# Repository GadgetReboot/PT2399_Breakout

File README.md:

# PT2399_Breakout
PT2399 Echo IC Breakout Board 
<br><br><BR><BR>

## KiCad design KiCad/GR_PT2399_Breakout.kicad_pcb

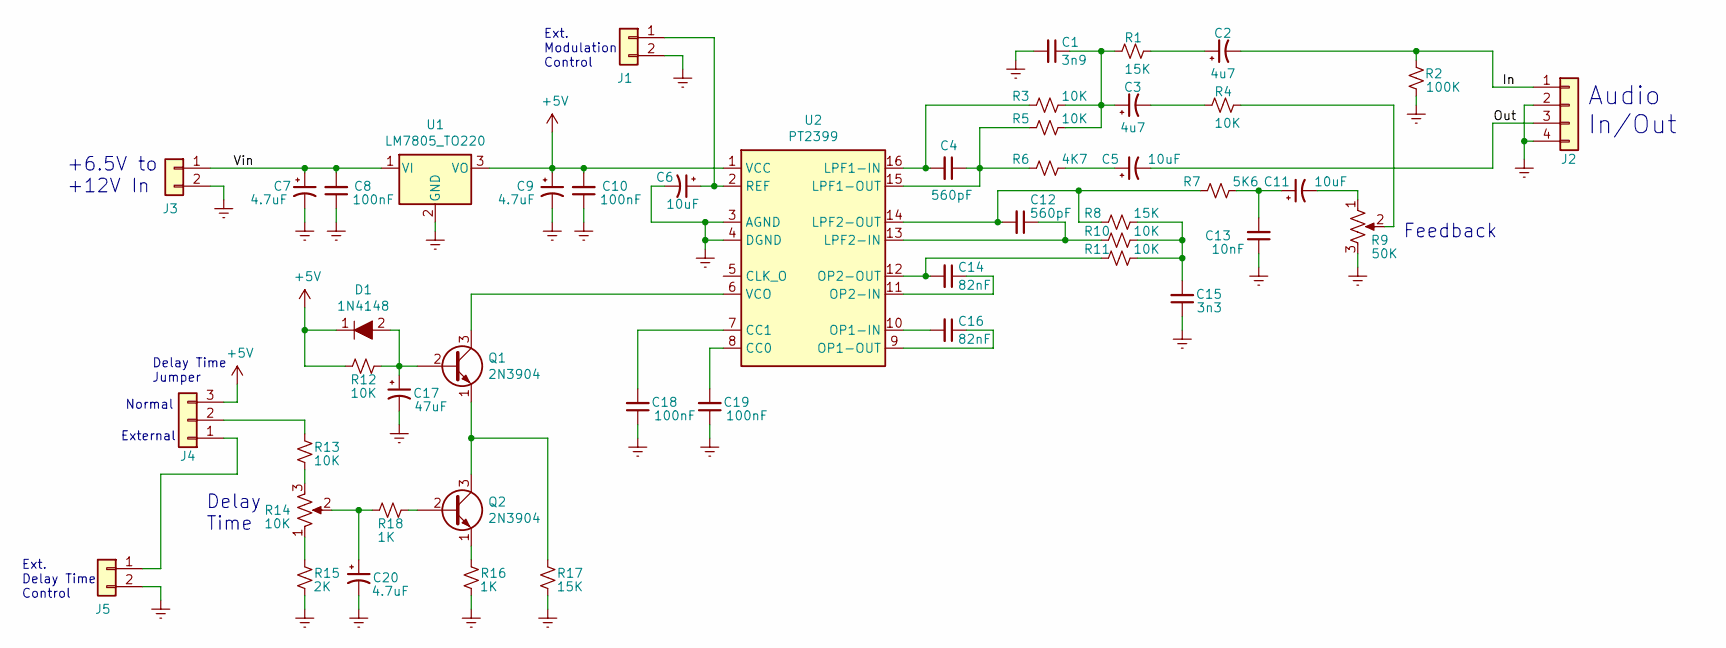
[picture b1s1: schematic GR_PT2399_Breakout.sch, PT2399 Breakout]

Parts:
C1: 3n9; C_Disc_D3.8mm_W2.6mm_P2.50mm
C2, C3: 4u7; CP_Radial_D5.0mm_P2.50mm
C4, C12: 560pF; C_Disc_D3.8mm_W2.6mm_P2.50mm
C5, C6, C11: 10uF; CP_Radial_D5.0mm_P2.50mm
C7, C9, C20: 4.7uF; CP_Radial_D5.0mm_P2.50mm
C8, C10, C18, C19: 100nF; C_Disc_D3.8mm_W2.6mm_P2.50mm
C13: 10nF; C_Disc_D3.8mm_W2.6mm_P2.50mm
C14, C16: 82nF; C_Disc_D3.8mm_W2.6mm_P2.50mm
C15: 3n3; C_Disc_D3.8mm_W2.6mm_P2.50mm
C17: 47uF; CP_Radial_D5.0mm_P2.50mm
D1: 1N4148; Diode_DO-35_P10mm; MPN 1N4148; Digi-Key_PN 1N4148FS-ND
J1, J3, J5: Conn_01x02; PinHeader_1x02_P2.54mm_Vertical
J2: Conn_01x04; PinHeader_1x04_P2.54mm_Vertical
J4: Conn_01x03; PinHeader_1x03_P2.54mm_Vertical
Q1, Q2: 2N3904; TO-92_Inline_Wide
R1, R8, R17: 15K; R_Axial_DIN0207_L6.3mm_D2.5mm_P10.16mm_Horizontal
R2: 100K; R_Axial_DIN0207_L6.3mm_D2.5mm_P10.16mm_Horizontal
R3, R4, R5, R10, R11, R12, R13: 10K; R_Axial_DIN0207_L6.3mm_D2.5mm_P10.16mm_Horizontal
R6: 4K7; R_Axial_DIN0207_L6.3mm_D2.5mm_P10.16mm_Horizontal
R7: 5K6; R_Axial_DIN0207_L6.3mm_D2.5mm_P10.16mm_Horizontal
R9: 50K; Potentiometer_Bourns_PTV09A-1
R14: 10K; Potentiometer_Bourns_PTV09A-1
R15: 2K; R_Axial_DIN0207_L6.3mm_D2.5mm_P10.16mm_Horizontal
R16, R18: 1K; R_Axial_DIN0207_L6.3mm_D2.5mm_P10.16mm_Horizontal
U1: LM7805_TO220; TO-220-3_Vertical
U2: PT2399; DIP-16_W7.62mm_Socket_LongPads

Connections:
+5V: C9.1, C10.2, D1.1, J4.3, R12.1, U1.3 (VO), U2.1 (VCC)
/In: C2.2, J2.1, R2.1
/Out: C5.2, J2.3
/Vin: C7.1, C8.2, J3.1, U1.1 (VI)
GNDREF: C1.2, C6.2, C7.2, C8.1, C9.2, C10.1, C13.1, C15.1, C17.2, C18.1, C19.1, C20.2, J1.2, J2.2, J2.4, J3.2, J5.2, R2.2, R9.3, R15.2, R16.2, R17.2, U1.2 (GND), U2.3 (AGND), U2.4 (DGND)
unnamed: C1.1, C3.1, R1.1, R3.2, R5.2
unnamed: C2.1, R1.2
unnamed: C3.2, R4.1
unnamed: C4.1, R5.1, R6.1, U2.15 (LPF1-OUT)
unnamed: C4.2, R3.1, U2.16 (LPF1-IN)
unnamed: C5.1, R6.2
unnamed: C6.1, J1.1, U2.2 (REF)
unnamed: C11.1, C13.2, R7.2
unnamed: C11.2, R9.1
unnamed: C12.1, R10.1, U2.13 (LPF2-IN)
unnamed: C12.2, R7.1, R8.1, U2.14 (LPF2-OUT)
unnamed: C14.1, U2.11 (OP2-IN)
unnamed: C14.2, R11.1, U2.12 (OP2-OUT)
unnamed: C15.2, R8.2, R10.2, R11.2
unnamed: C16.1, U2.9 (OP1-OUT)
unnamed: C16.2, U2.10 (OP1-IN)
unnamed: C17.1, D1.2, Q1.2 (B), R12.2
unnamed: C18.2, U2.7 (CC1)
unnamed: C19.2, U2.8 (CC0)
unnamed: C20.1, R14.2, R18.1
unnamed: J4.1, J5.1
unnamed: J4.2, R13.1
unnamed: Q1.1 (E), Q2.3 (C), R17.1
unnamed: Q1.3 (C), U2.6 (VCO)
unnamed: Q2.1 (E), R16.1
unnamed: Q2.2 (B), R18.2
unnamed: R4.2, R9.2
unnamed: R13.2, R14.3
unnamed: R14.1, R15.1

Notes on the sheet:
Audio In/Out
Delay Time Jumper
Delay Time
Normal
External
+6.5V to +12V In
Ext. Delay Time Control
Ext. Modulation Control
Feedback

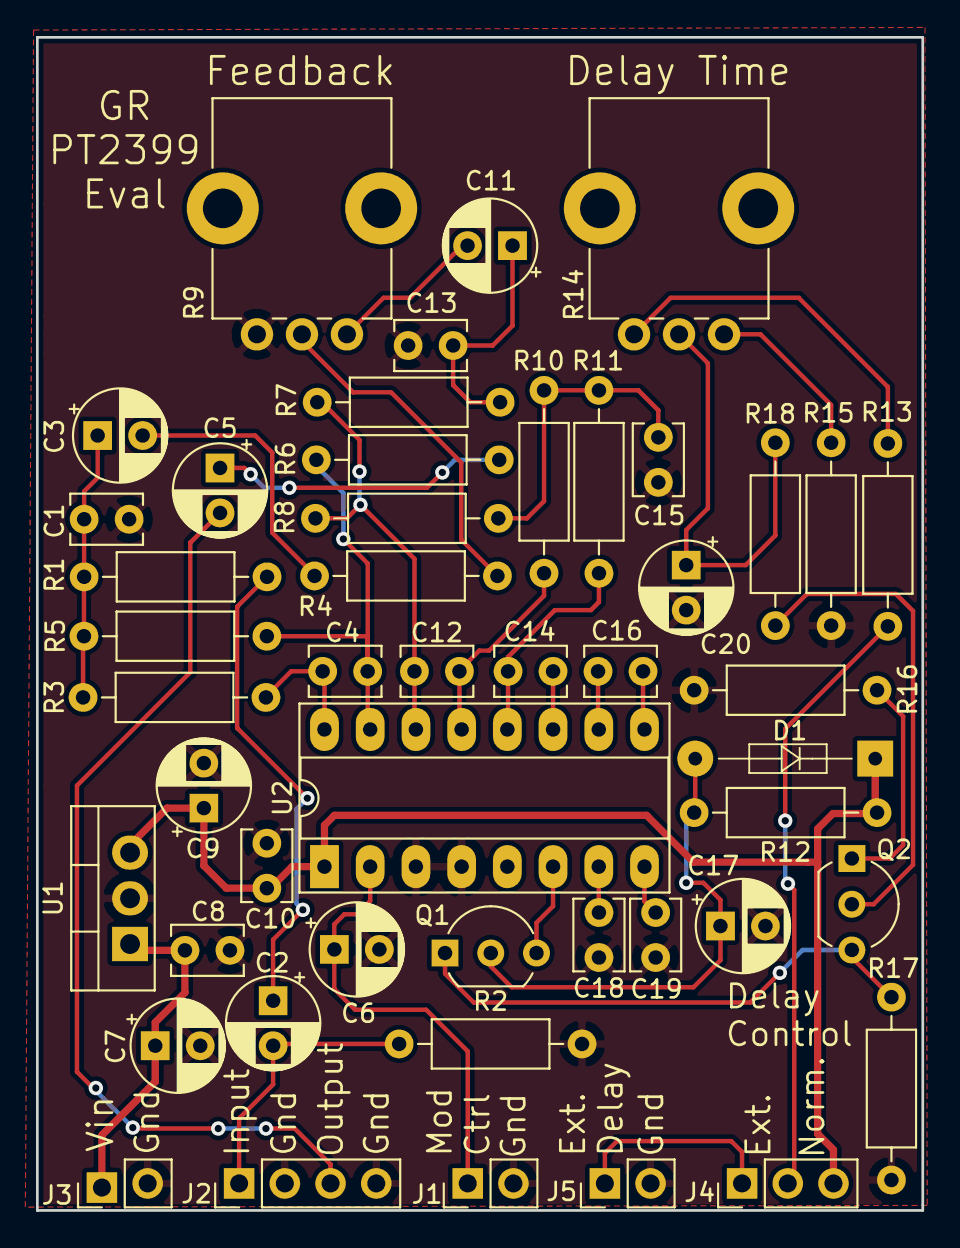
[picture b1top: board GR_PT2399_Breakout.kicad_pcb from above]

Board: 2 copper layers, 49.2 x 65.2 mm, 48 parts (0 on the bottom side), 34 nets.
